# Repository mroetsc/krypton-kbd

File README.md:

# Krypton-KBD

Ergonmic split keyboard created with [ergogen](https://github.com/ergogen/ergogen).

Named after the noble gas [krypton](https://en.wikipedia.org/wiki/Krypton).

## Features
* Completely wireless with support for wired
* One rotary encoder per half
* Num row
* Ergonomic, easily reachable thumb cluster, also ideal for larger hands
* 3D-printed case (open and closed versions) and switchplate
* Support for [ZMK Studio](https://zmk.dev/docs/features/studio), allowing keymap changes without reflashing
* Support for nice!view displays

## Images

# Build instructions
The build instructions can be found [here](https://github.com/mroetsc/krypton-kbd/blob/main/docs/build_instructions.md).

## Keymap
The default keymap is for Colemak-DH. It can easily be changed using [ZMK Studio](https://zmk.dev/docs/features/studio).

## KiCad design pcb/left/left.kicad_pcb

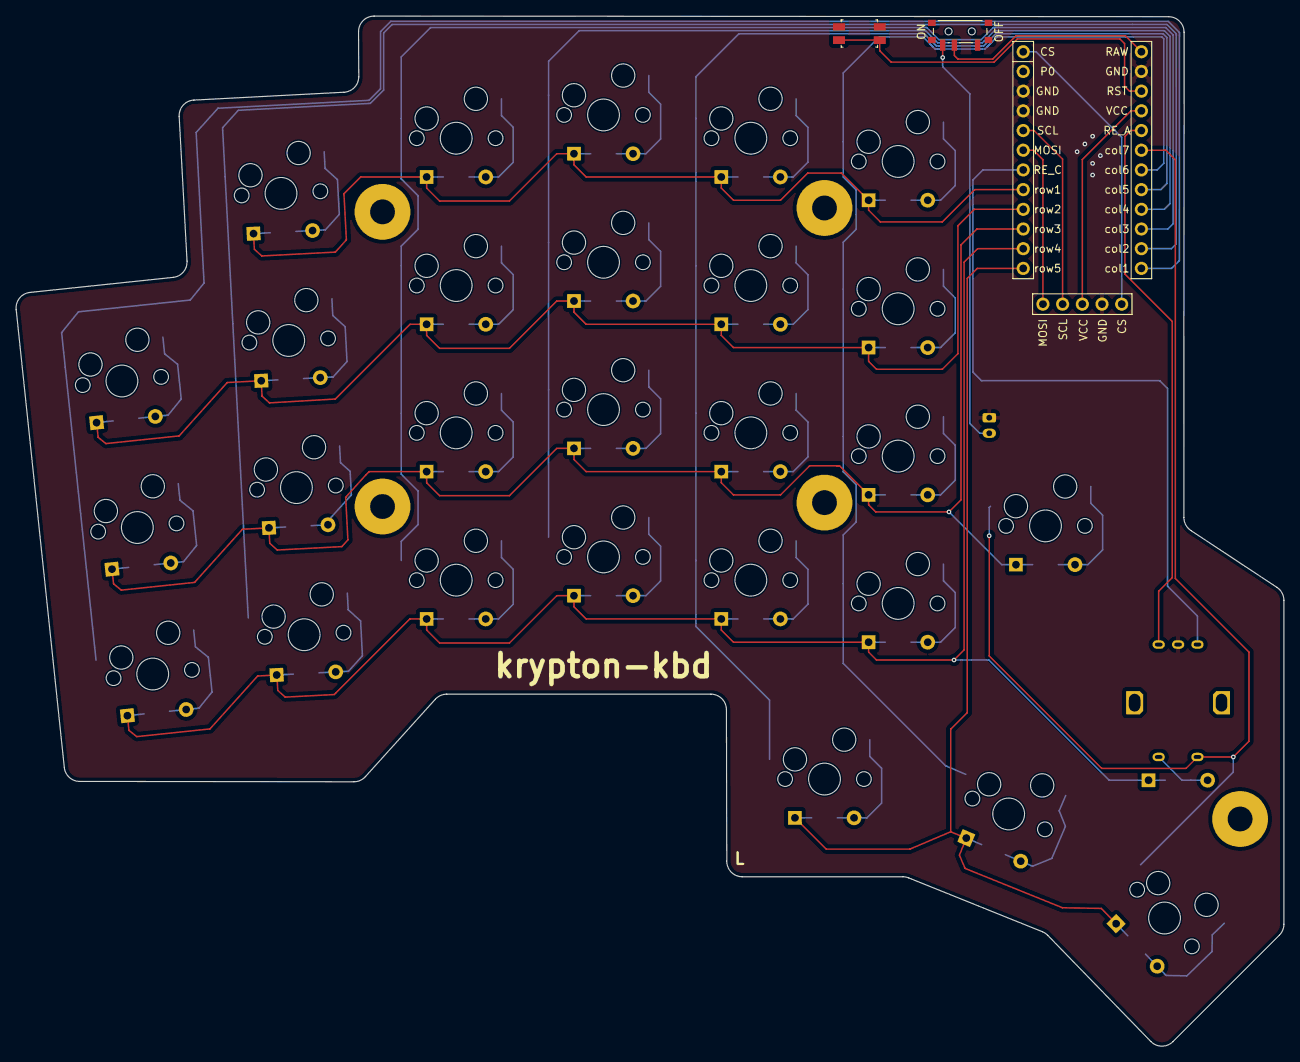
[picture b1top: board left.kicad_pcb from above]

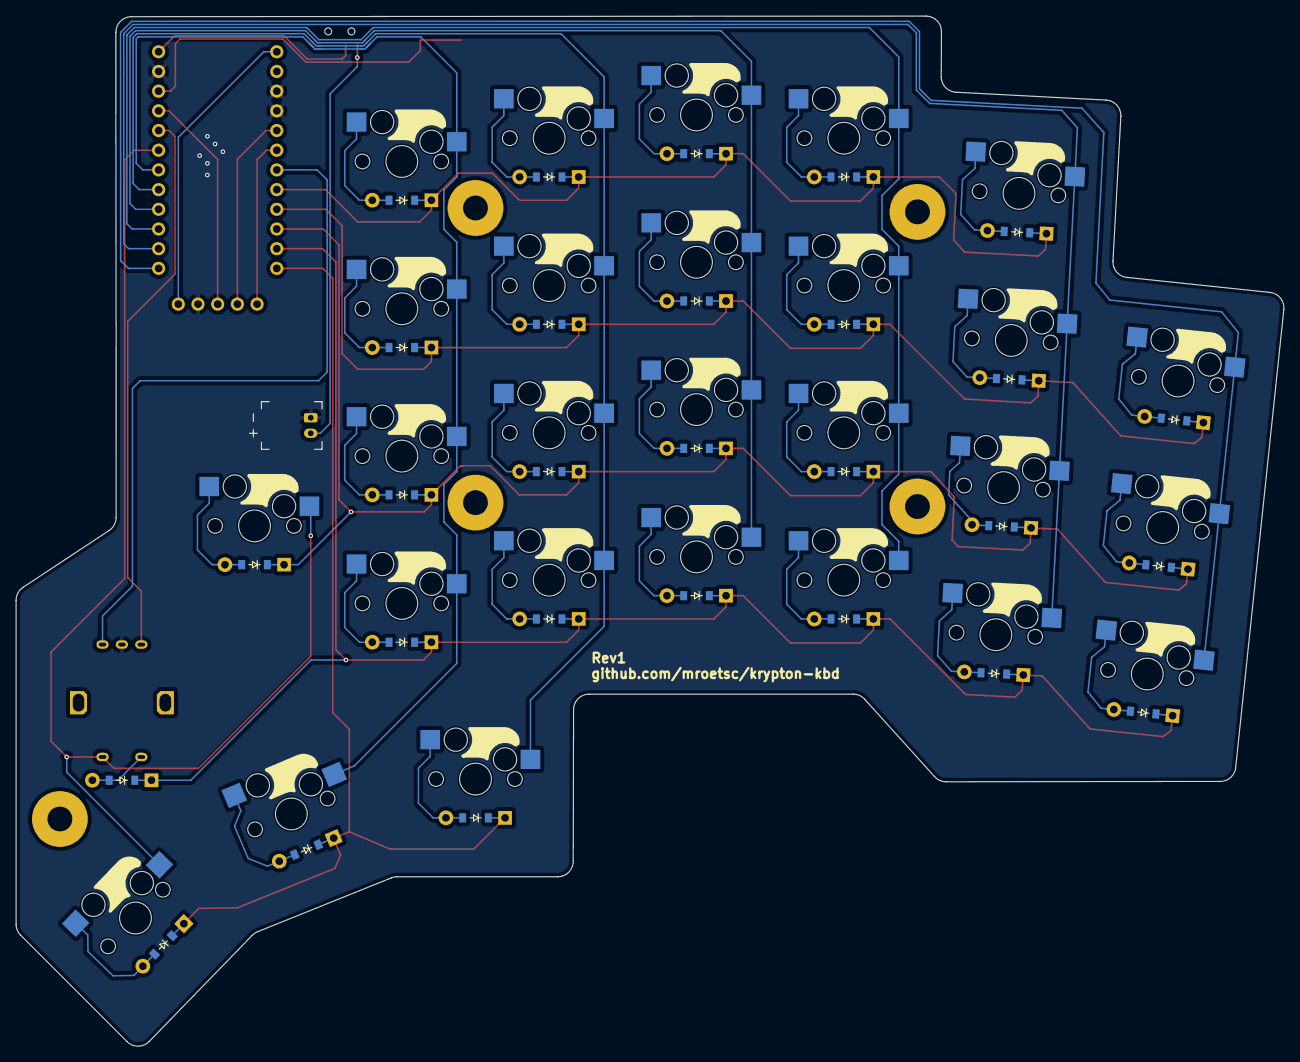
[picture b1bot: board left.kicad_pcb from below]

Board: 2 copper layers, 163.5 x 132.8 mm, 66 parts (56 on the bottom side), 50 nets.

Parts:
D1, D2, D3, D4, D5, D6, D7, D8, D9, D10, D11, D12, D13, D14, D15, D16, D17, D18, D19, D20, D21, D22, D23, D24, D25, D26, D27, D28: diode_tht_sod123
DISP1: display_nice_view
H1, H2, H3, H4, H5: mounting_hole_plated
JST1: battery_connector_jst_ph_2
MCU1: mcu_nice_nano
PWR1: power_switch_smd_side
RE1: rotary_encoder_ec11_ec12
RST1: reset_switch_smd_side
S1, S2, S3, S4, S5, S6, S7, S8, S9, S10, S11, S12, S13, S14, S15, S16, S17, S18, S19, S20, S21, S22, S23, S24, S25, S26, S27: switch_mx

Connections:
BAT_P: JST1.2, PWR1.3
CS: DISP1.5, MCU1.24
GND: DISP1.4, JST1.1, MCU1.2, MCU1.21, MCU1.22, RE1.B, RST1.1, RST1.3
MOSI: DISP1.1, MCU1.19
RAW: MCU1.1, PWR1.2
RE_A: MCU1.5, RE1.A
RE_C: MCU1.18, RE1.C
RST: MCU1.3, RST1.2, RST1.4
SCL: DISP1.2, MCU1.20
VCC: DISP1.3, MCU1.4
brackets_home: D24.2, S24.2
col1: MCU1.12, S1.1, S2.1, S3.1
col2: MCU1.11, S4.1, S5.1, S6.1, S7.1
col3: MCU1.10, S8.1, S9.1, S10.1, S11.1
col4: MCU1.9, S12.1, S13.1, S14.1, S15.1
col5: MCU1.8, S16.1, S17.1, S18.1, S19.1, S25.1
col6: MCU1.7, S20.1, S21.1, S22.1, S23.1, S26.1
col7: MCU1.6, RE1.S1, S24.1, S27.1
encoder_encoder: D28.2, RE1.S2
index_bottom: D16.2, S16.2
index_home: D17.2, S17.2
index_num: D19.2, S19.2
index_top: D18.2, S18.2
inner_bottom: D20.2, S20.2
inner_home: D21.2, S21.2
inner_num: D23.2, S23.2
inner_top: D22.2, S22.2
layer_cluster: D27.2, S27.2
middle_bottom: D12.2, S12.2
middle_home: D13.2, S13.2
middle_num: D15.2, S15.2
middle_top: D14.2, S14.2
pinky_bottom: D4.2, S4.2
pinky_home: D5.2, S5.2
pinky_num: D7.2, S7.2
pinky_top: D6.2, S6.2
ring_bottom: D8.2, S8.2
ring_home: D9.2, S9.2
ring_num: D11.2, S11.2
ring_top: D10.2, S10.2
row1: D7.1, D11.1, D15.1, D19.1, D23.1, MCU1.17
row2: D3.1, D6.1, D10.1, D14.1, D18.1, D22.1, MCU1.16
row3: D2.1, D5.1, D9.1, D13.1, D17.1, D21.1, D24.1, MCU1.15
row4: D1.1, D4.1, D8.1, D12.1, D16.1, D20.1, D28.1, MCU1.14
row5: D25.1, D26.1, D27.1, MCU1.13
space_cluster: D26.2, S26.2
stretch_bottom: D1.2, S1.2
stretch_home: D2.2, S2.2
stretch_top: D3.2, S3.2
super_cluster: D25.2, S25.2

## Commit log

2024-11-17 feat(ergogen): Added first config draft
2024-11-18 docs: Updated README
2024-11-18 feat(points): Refined base layout
2024-11-21 feat(points): Added oled and encoder
2024-11-23 feat(outlines): Started on outlines
2024-11-23 feat(pcb): testing pcb with first draft
2025-02-10 chore: added ceolide footprints as submodule
2025-02-11 feat: began rework
    did rough points
2025-02-11 feat: minor touch up of points
2025-02-22 feat: refined layout; added num row, removed screen
2025-02-23 feat: finished preliminary outline
2025-02-23 feat: started with pcb
2025-02-25 feat: Added more footprints
2025-02-25 Updated roadmap
2025-02-25 Began with nets
2025-02-26 Modified nets on nice nano and encoder
2025-02-26 Shoulve fixed nets for encoder
2025-02-28 Switched footprints to ceoloide and added 3d models
2025-03-01 Fixed colors of switches and nice nano 3d models
2025-03-01 Added watcher script to auto run on file update
2025-03-01 Reworked outlines
2025-03-01 Edited reset and power switch footprints to match new outlines
2025-03-01 Added conversion of jscad to stl to watcher script
2025-03-01 Added output dir to gitignore for now
2025-03-01 Added encoder with knob cad file
2025-03-01 Overhauled thumb cluster
2025-03-01 Added simple case to test layout
2025-03-02 Added option for nice view
2025-03-02 Straightened outlines
2025-03-02 Moved nice nano and power switch closer to edge
2025-03-02 Updated readme and added in progress picture
2025-03-03 Moved battery connector a bit
2025-03-04 Added mounting holes
2025-03-04 Began work with case
2025-03-05 Updated ceoloide footprints submodule to latest ref
2025-03-05 Excluded some outlines from export
2025-03-05 Changed dir structure
2025-03-05 Added switchplate and mounting holes, changed how case will be created
    only creating switchplate and bottom area with ergogen, rest in freecad
2025-03-05 Added cad sources and fixed power switch colors
2025-03-05 Added right half
2025-03-05 Added build instruction placeholder
2025-03-06 Added encoder cutout to switchplate
2025-03-06 Added basic routing for most common tracks on left side
    inner key, columns, rows
2025-03-06 Added text with keyboard name on front side to distinguish halfes
2025-03-06 Basic routing for right side in progress
2025-03-07 Added basic routing of rows for right side
2025-03-07 Changed encoder row net and fixed net for right side
2025-03-07 Added zmk firmware as submodule
2025-03-09 Updated firmware submodule ref
2025-03-09 Added kicad and freecad gitignore
2025-03-09 Began with case files
2025-03-09 Fixed outer right mounting hole misalignment and changed switchplate and bottom thickness
2025-03-09 Imported models into case
2025-03-10 Modified left col pins to make routing easier
2025-03-10 Finished preliminary routing for left side
2025-03-11 Minor adjustments to pcb routing
2025-03-13 Added note about ec11 footprint
2025-03-13 Updated firmware module ref
2025-04-06 Chaged pcb dir structure
2025-04-06 Modified right row pins for easier routing
2025-04-06 Set pre-routed tracks with
2025-04-06 Redid left routing
2025-04-06 Finished routing for right side
2025-04-06 Added proper sheet names
2025-04-06 Set gerber and drill output dir
2025-04-07 Added cutout for mcu to switchplate
2025-04-07 Restructured case dir
2025-04-07 Fixed pcb hole diameter and bottom plate screws
2025-04-08 wip: rough case alignments
2025-04-09 Fixed mounting hole diameter and position
    top and bottom right mounting hole was too small for standoff and in the
    way of the pad once adjusted; also increased pad size to match 3d
    printed standoff from bottom
2025-04-09 Refined pcb routing, fixed hole issue on pcb
2025-04-09 Generated production files
2025-04-13 Updated base models for case
2025-04-15 Finished rough shape of case bottom
2025-04-15 Adjusted nice nano model height in pcb
2025-04-16 Started with case io cutouts
2025-04-23 Created case without outer walls
2025-04-25 Removed obsolete note from readme
2025-04-25 Updated firmware ref
2025-04-28 Changed bottom plate to 3mm and reduced space between plate and PCB on case without walls
2025-04-28 Added bumper mounting guides to open case
2025-04-28 Renamed case files
2025-04-29 Changed bottom plate to 3mm on closed case
2025-04-29 Added io cutouts to closed case
2025-04-29 Added bumper mounting guide to closed case
2025-04-30 Adjusted freecad model outlines
2025-04-30 Added pocket for easier battery mounting to cases
2025-05-01 Added keymap drawing
2025-05-10 Added exported case files
2025-05-10 Wrote build guide and reworked readme
2025-05-28 Upated keymap image and firmware submodule ref (v0.0.5)
2025-05-29 Updated keyboard image and submodule ref for v0.0.6
2025-06-04 Fixed typo and added better case description in README
